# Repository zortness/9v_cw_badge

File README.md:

# 9V QRP BADGE Transciever

Based on the schematic and work of Jeff Anderson, [K6JCA](https://www.qrz.com/db/k6jca)
and [this blog post](http://k6jca.blogspot.com/2009/08/9v-qrp-transceiver.html).

Variant of the smaller [9V battery-sized version](https://github.com/zortness/9v_cw_tx).

## About

This is a very simple, direct conversion CW transciever that will operate on the 40m 
amateur radio band. It requires an external speaker or headphones, an external antenna,
and a power source between 5 and 12 volts.

**This is still a work in progress.**

Changes from the micro version:
* larger credit card or badge size (55mm X 85mm)
* includes 7-element low pass filter (LPF) based on the QCX design with T-37-2 toroids
* includes ATTiny402 to control keying output, and reading buttons
* includes buttons for DIT and DAH 
* includes 9x2 header pinout for exposing and adding functionality (or fancy covering)

## Schematics

## Board Layouts

## SMD BOM

** WIP **

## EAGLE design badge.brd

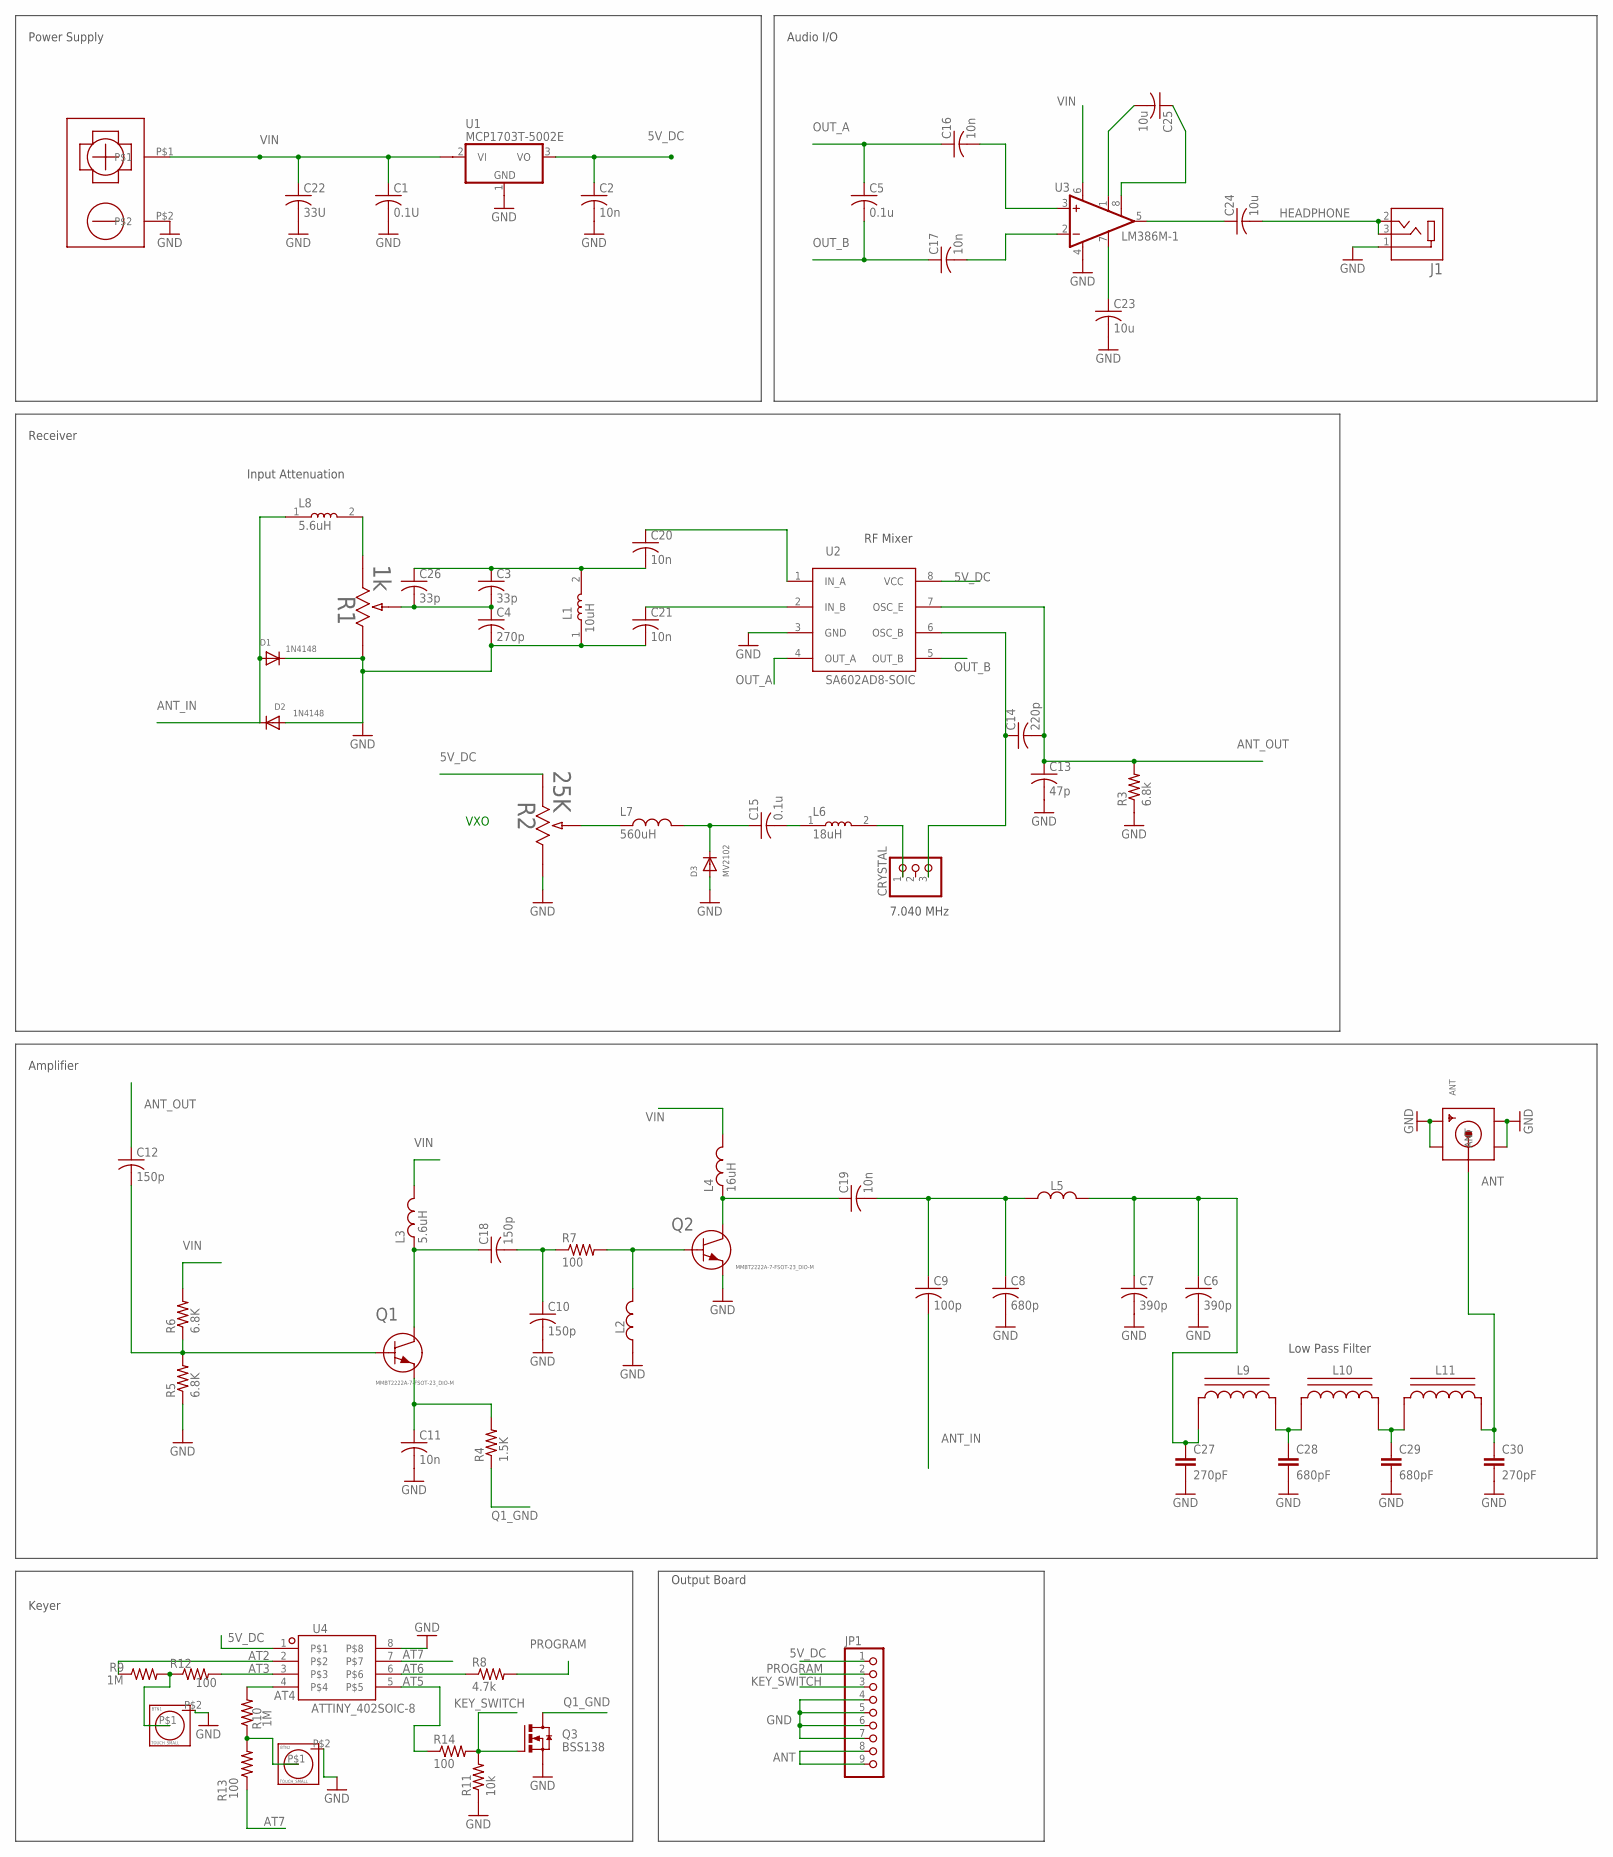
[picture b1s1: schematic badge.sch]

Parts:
ANT: SMACONNECTOR_EDGE; SMA_EDGELAUNCH
BTN1, BTN2: TOUCH_SMALL
C1: 0.1U; C0805
C2, C11, C16, C17, C20, C21: 10n; C0805
C3, C26: 33p; C0805
C4: 270p; C0805
C5, C15: 0.1u; C0805
C6, C7: 390p; C0805
C8: 680p; C0805
C9: 100p; C0805
C10, C12, C18: 150p; C0805
C13: 47p; C0805
C14: 220p; C0805
C19: 10n; C1206
C22: 33U; C1206
C23, C24, C25: 10u; C0805
C27, C30: 270pF; 1206
C28, C29: 680pF; 1206
CRYSTAL: PINHD-1X3; 1X03
D1, D2: 1N4148; SOD-123FL
D3: MV2102; SOD-323F
J1: SJ-3523-SMT-TR; CUI_SJ-3523-SMT-TR
JP1: PINHD-1X9; 1X09-BIG
L1: 10uH; INDC2012X87N
L2: L_CHIP-1008(2520-METRIC); INDC2520X120N
L3: 5.6uH; SRP3012C
L4: 16uH; ASPI-0630LR
L5: 1.2uH; SRN4018TA
L6: 18uH; INDC2012X87N
L7: 560uH; INDM4532X32_W
L8: 5.6uH; INDC2012X87N
L9, L11: 1.38uH; T37_INDUCTOR
L10: 1.67uH; T37_INDUCTOR
Q1, Q2: MMBT2222A-7-FSOT-23_DIO-M; SOT-23_DIO-M
Q3: BSS138; SOT23-3
R1: 1k; POT_3362W
R2: 25K; POT_3362W
R3: 6.8k; M0805
R4: 1.5K; M0805
R5, R6: 6.8K; M0805
R7, R12, R13, R14: 100; M0805
R8: 4.7k; M0805
R9, R10: 1M; M0805
R11: 10k; M0805
U1: MCP1703T-5002E; SOT89
U2: SA602AD8-SOIC; SOIC127P599X175-8N
U3: LM386M-1; SO08
U4: ATTINY_402SOIC-8; SOIC127P599X175-8N
U$1: 9V_9689V_968_SMD; 9V_968_PAD

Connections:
5V_DC: C2.1, JP1.1, R2.1, U1.3 (VO), U2.8 (VCC), U4.1
ANT: ANT.P (ANT), C30.1, JP1.8, JP1.9, L11.CA
ANT_IN: C9.2, D1.A, D2.C, L8.1
ANT_OUT: C12.1, C13.1, C14.2, R3.2, U2.7 (OSC_E)
AT2: R9.1, U4.2
AT3: R12.2, U4.3
AT4: R10.2, U4.4
AT5: R14.1, U4.5
AT6: R8.1, U4.6
AT7: R13.1, U4.7
GND: ANT.GND@1 (GND4), ANT.GND@3 (GND2), BTN1.P$2, BTN2.P$2, C1.2, C2.2, C4.2, C6.2, C7.2, C8.2, C10.2, C11.2, C13.2, C21.2, C22.2, C23.2, C27.2, C28.2, C29.2, C30.2, D1.C, D2.A, D3.A, J1.1, JP1.4, JP1.5, JP1.6, JP1.7, L1.1, L2.1, Q3.2 (S), R1.3, R2.3, R3.1, R5.1, R11.1, U1.1 (GND), U2.3 (GND), U3.4 (GND), U4.8, U$1.P$2
HEADPHONE: C24.2, J1.2, J1.3
KEY_SWITCH: JP1.3, Q3.1 (G), R11.2, R14.2
unnamed: C20.1, U2.1 (IN_A)
unnamed: C21.1, U2.2 (IN_B)
unnamed: C3.1, C20.2, C26.1, L1.2
unnamed: C3.2, C4.1, C26.2, R1.2
unnamed: L8.2, R1.1
unnamed: C14.1, CRYSTAL.3, U2.6 (OSC_B)
unnamed: C16.2, U3.3 (+IN)
unnamed: C17.2, U3.2 (-IN)
unnamed: C23.1, U3.7 (BYPASS)
unnamed: C25.1, U3.8 (GAIN)
unnamed: C25.2, U3.1 (GAIN)
unnamed: C24.1, U3.5 (OUT)
unnamed: CRYSTAL.1, L6.2
unnamed: C15.2, L6.1
unnamed: C15.1, D3.C, L7.2
unnamed: L7.1, R2.2
unnamed: C12.2, Q1.1, R5.2, R6.1
unnamed: C11.1, Q1.2 (3), R4.2
unnamed: C18.1, L3.P$1 (1), Q1.3 (2)
unnamed: C10.1, C18.2, R7.1
unnamed: L2.2, Q2.1, R7.2
unnamed: C19.1, L4.P$1 (1), Q2.3 (2)
unnamed: C8.1, C9.1, C19.2, L5.P$1 (1)
unnamed: C6.1, C7.1, C27.1, L5.P$2 (2), L9.CB
unnamed: BTN1.P$1, R9.2, R12.1
unnamed: C28.1, L9.CA, L10.CB
unnamed: C29.1, L10.CA, L11.CB
unnamed: BTN2.P$1, R10.1, R13.2
OUT_A: C5.1, C16.1, U2.4 (OUT_A)
OUT_B: C5.2, C17.1, U2.5 (OUT_B)
PROGRAM: JP1.2, R8.2
Q1_GND: Q3.3 (D), R4.1
VIN: C1.1, C22.1, L3.P$2 (2), L4.P$2 (2), R6.2, U1.2@1 (VI1), U3.6 (VS), U$1.P$1

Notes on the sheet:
Power Supply
Audio I/O
Input Attenuation
RF Mixer
VXO
7.040 MHz
Receiver
Amplifier
Low Pass Filter
Keyer
Output Board

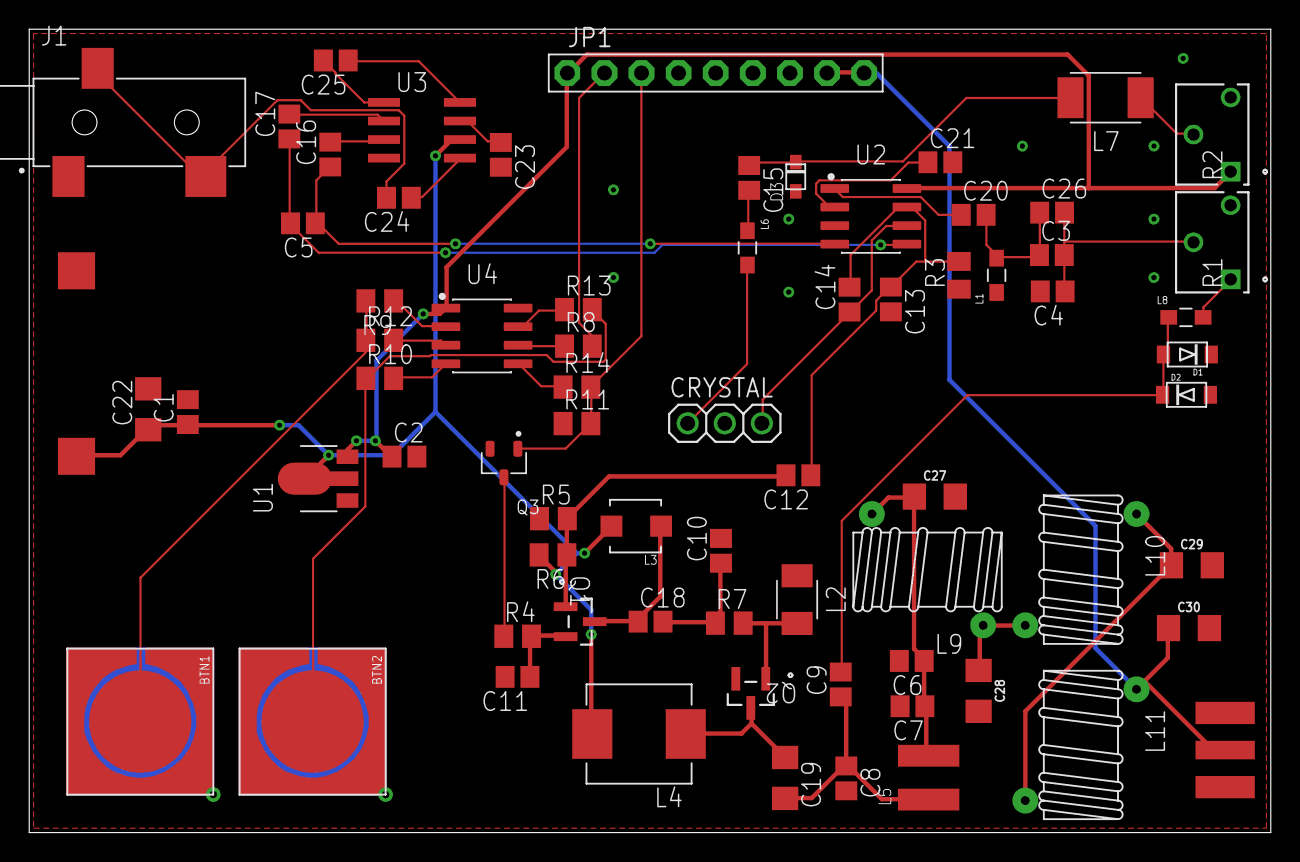
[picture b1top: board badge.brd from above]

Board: 2 copper layers, 85.0 x 55.0 mm, 72 parts (0 on the bottom side), 46 nets.

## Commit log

2020-12-23 initial commit
    * clone of the 9V TX
    * added a low pass filter on the output
    Still to do
    * ATTiny keyer
    * buttons
2020-12-24 updates
    * added ATTiny keyer and buttons
    * added breakout jumper
    * added images
    * added README
2020-12-24 Update README.md
    removing some extraneous stuff from README
2020-12-28 moving to capacitive touch
    Not ready for production
    * replaced switches with capacitive touch buttons
    * slight cleanup pass

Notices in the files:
parts and their libraries:
SparkFun-Capacitors: Licensing: Creative Commons ShareAlike 4.0 International - https://creativecommons.org/licenses/by-sa/4.0
